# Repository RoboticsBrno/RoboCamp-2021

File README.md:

View this project on [CADLAB.io](https://cadlab.io/project/24548). 

# RoboCamp-2021

Podklady a web k Robotickému táboru 2021. 

K dispozici na [2021.robotickytabor.cz](https://2021.robotickytabor.cz/).

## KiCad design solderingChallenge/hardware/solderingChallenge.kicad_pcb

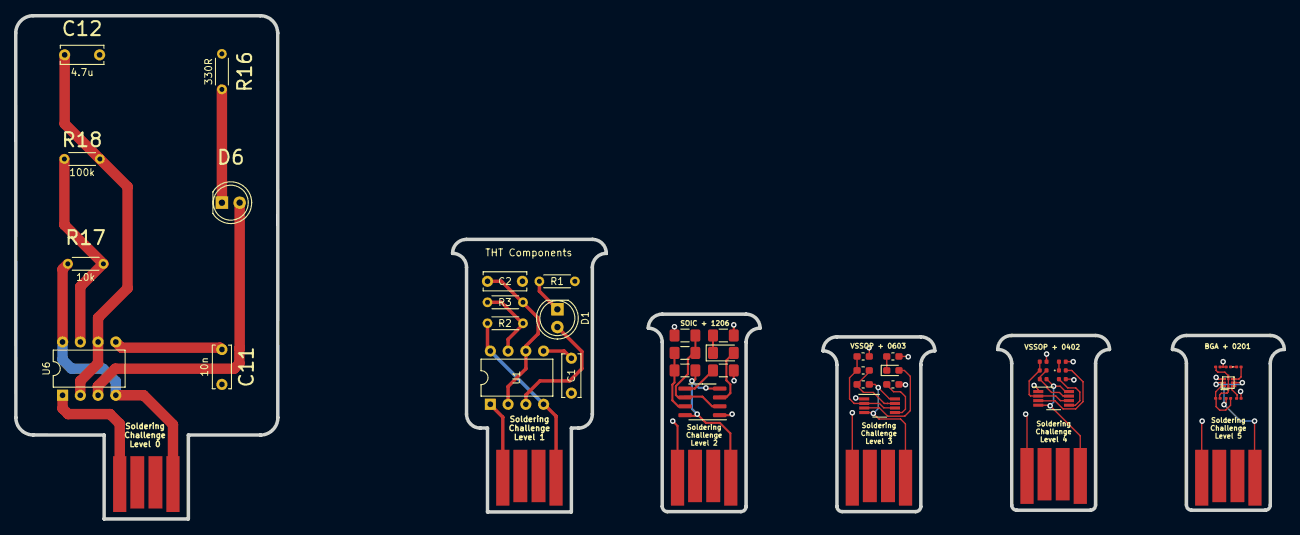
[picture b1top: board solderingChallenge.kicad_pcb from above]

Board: 2 copper layers, 181.5 x 72.0 mm, 54 parts (0 on the bottom side), 42 nets.

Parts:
B0, B1, B2, B3, B4, B5: Board
C1, C11: 10n; C_Disc_D6.0mm_W2.5mm_P5.00mm
C2, C12: 4.7u; C_Disc_D6.0mm_W2.5mm_P5.00mm
C3: 10n; C_1206_3216Metric_Pad1.42x1.75mm_HandSolder
C4: 4.7u; C_1206_3216Metric_Pad1.42x1.75mm_HandSolder
C5: 10n; C_0603_1608Metric_Pad1.05x0.95mm_HandSolder
C6: 4.7u; C_0603_1608Metric_Pad1.05x0.95mm_HandSolder
C7: 10n; C_0402_1005Metric
C8: 4.7u; C_0402_1005Metric
C9: 10n; C_0201_0603Metric
C10: 4.7u; C_0201_0603Metric
D1, D6: LED; LED_D5.0mm
D2: LED; LED_1206_3216Metric_Pad1.42x1.75mm_HandSolder
D3: LED; LED_0603_1608Metric_Pad1.05x0.95mm_HandSolder
D4: LED; LED_0402_1005Metric
D5: LED; LED_0201_0603Metric
J1, J2, J4, J6, J8, J10: USB_A; usb-PCB
R1, R16: 330R; R_Axial_DIN0204_L3.6mm_D1.6mm_P5.08mm_Horizontal
R2, R17: 10k; R_Axial_DIN0204_L3.6mm_D1.6mm_P5.08mm_Horizontal
R3, R18: 100k; R_Axial_DIN0204_L3.6mm_D1.6mm_P5.08mm_Horizontal
R4: 330R; R_1206_3216Metric_Pad1.42x1.75mm_HandSolder
R5: 10k; R_1206_3216Metric_Pad1.42x1.75mm_HandSolder
R6: 100k; R_1206_3216Metric_Pad1.42x1.75mm_HandSolder
R7: 330R; R_0603_1608Metric_Pad1.05x0.95mm_HandSolder
R8: 10k; R_0603_1608Metric_Pad1.05x0.95mm_HandSolder
R9: 100k; R_0603_1608Metric_Pad1.05x0.95mm_HandSolder
R10: 330R; R_0402_1005Metric
R11: 10k; R_0402_1005Metric
R12: 100k; R_0402_1005Metric
R13: 330R; R_0201_0603Metric
R14: 10k; R_0201_0603Metric
R15: 100k; R_0201_0603Metric
U1, U6: LM555xN; DIP-8_W7.62mm
U2: LMC555xM; SOIC-8_3.9x4.9mm_P1.27mm
U3, U4: LMC555xMM; VSSOP-8_3.0x3.0mm_P0.65mm
U5: LMC555xTP; Texas_DSBGA-8_1.43x1.41mm_Layout3x3_P0.5mm

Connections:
/Level 0 - THT/GND: C11.2, C12.2, J1.4 (GND), R16.1, U6.1 (GND)
/Level 0 - THT/VCC: J1.1 (VBUS), R17.1, U6.4 (R), U6.8 (VCC)
/Level 1 - THT/GND: C1.2, C2.2, J2.4 (GND), R1.1, U1.1 (GND)
/Level 1 - THT/VCC: J2.1 (VBUS), R2.1, U1.4 (R), U1.8 (VCC)
/Level 2 - 1206/GND: C3.2, C4.2, J4.4 (GND), R4.1, U2.1 (GND)
/Level 2 - 1206/VCC: J4.1 (VBUS), R5.1, U2.4 (R), U2.8 (VCC)
/Level 3 - 0603/GND: C5.2, C6.2, J6.4 (GND), R7.1, U3.1 (GND)
/Level 3 - 0603/VCC: J6.1 (VBUS), R8.1, U3.4 (R), U3.8 (VCC)
/Level 4 - 0402/GND: C7.2, C8.2, J8.4 (GND), R10.1, U4.1 (GND)
/Level 4 - 0402/VCC: J8.1 (VBUS), R11.1, U4.4 (R), U4.8 (VCC)
/Level 5 - 0201/GND: C9.2, C10.2, J10.4 (GND), R13.1, U5.A3 (GND)
/Level 5 - 0201/VCC: J10.1 (VBUS), R14.1, U5.A2 (VCC), U5.C2 (R)
unnamed: C1.1, U1.5 (CV)
unnamed: C2.1, R3.2, U1.2 (TR), U1.6 (THR)
unnamed: C3.1, U2.5 (CV)
unnamed: C4.1, R6.2, U2.2 (TR), U2.6 (THR)
unnamed: C5.1, U3.5 (CV)
unnamed: C6.1, R9.2, U3.2 (TR), U3.6 (THR)
unnamed: C7.1, U4.5 (CV)
unnamed: C8.1, R12.2, U4.2 (TR), U4.6 (THR)
unnamed: C9.1, U5.C1 (CV)
unnamed: C10.1, R15.2, U5.B1 (THR), U5.B3 (TR)
unnamed: C11.1, U6.5 (CV)
unnamed: C12.1, R18.2, U6.2 (TR), U6.6 (THR)
unnamed: D1.1 (K), R1.2
unnamed: D1.2 (A), U1.3 (Q)
unnamed: D2.1 (K), R4.2
unnamed: D2.2 (A), U2.3 (Q)
unnamed: D3.1 (K), R7.2
unnamed: D3.2 (A), U3.3 (Q)
unnamed: D4.1 (K), R10.2
unnamed: D4.2 (A), U4.3 (Q)
unnamed: D5.1 (K), R13.2
unnamed: D5.2 (A), U5.C3 (Q)
unnamed: D6.1 (K), R16.2
unnamed: D6.2 (A), U6.3 (Q)
unnamed: R2.2, R3.1, U1.7 (DIS)
unnamed: R5.2, R6.1, U2.7 (DIS)
unnamed: R8.2, R9.1, U3.7 (DIS)
unnamed: R11.2, R12.1, U4.7 (DIS)
unnamed: R14.2, R15.1, U5.A1 (DIS)
unnamed: R17.2, R18.1, U6.7 (DIS)

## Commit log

2020-12-13 Add template
2021-01-23 Draft first draft of smdChallenge
2021-01-24 Rename smdChallenge to solderingChallenge
2021-01-24 Finish first version of solderingChallenge
2021-02-03 Electronic Die schematic
2021-02-04 Add board
2021-02-04 Add silkscreen
2021-02-05 Add SMD power LED for testing purposes
2021-02-05 Fix +5V polygon
2021-02-05 Add mounting holes
2021-02-05 Set polygons isolation to 12 mils and width to 20 mils
2021-02-05 Add NC symbol to USB data pins
2021-02-05 Add dimensions
2021-02-05 Fix USB width
2021-02-05 Fix silkscreen layer
2021-02-05 Add JLCPCB order number location, fix SMD parts name font size
2021-02-05 Add CAM and DRU configuration
2021-02-05 Electronic Die v1.0
2021-02-11 Add v1.0 BOM (Mouser)
2021-03-22 Add RoboSvit
2021-03-22 Fix typo
2021-05-05 ElectronicDie: fix v1.0 problems - make it bigger - change resistors and diodes package size - make larger spaces between parts - minimize part types - fix PNP transistor pinout - remove SMD power LED
2021-06-03 Add target for gatema gerbers
2021-06-04 ElectronicDie v1.1 gerbers (removed JLCPCB order number label, because of fabrication in Gatema)
2021-06-08 Add USB pads
2021-06-09 Change Helceletka branding
2021-07-03 Remove extra level, add documentation
2021-07-07 Add RoboSvit Doc
2021-07-07 Remove two pictures
2021-07-07 Add CZ and EN manual link
2021-07-08 Add md doc for electron
2021-07-08 Edit schematic images
2021-07-08 Add Logic photo guide
2021-07-08 formulation
2021-07-08 Update electronicDie manual
2021-07-08 Fix electron 1. lesson - resistors
2021-07-08 Add electronicDie manual
2021-07-08 Add Logic text manual
2021-07-08 Minify images, add electronicDie manual
2021-07-08 Update schematic symbols in electron guide
2021-07-09 Add web doc
2021-07-09 Change electron schema color, resize roboSvit
2021-07-09 Add favicon, add logic fancy photos
2021-07-09 Resize electron, solderingCh images
2021-07-09 Fix typo, resize images
2021-07-09 Fix type errors and add whitespace to values
2021-07-09 Fix typos
2021-07-09 Last minute touches
2021-07-09 Empty commit
2021-07-09 Add BlackBox
2021-07-09 Fix more typos
2021-07-09 Fix typos in BlackBox
2021-07-09 Add BlackBox PDF guide
2021-07-09 add PCB of Logic
2021-07-09 Add fancy features
2021-07-09 Add note about polarity
2021-07-09 Add fancy design to index page
2021-07-09 Fix name mistake
2021-07-09 Add electron photos
2021-07-09 Add more fancy photos
2021-07-09 Add SMD fancy photo
2021-07-10 Add logo moustache
2021-07-11 Scale down ridiculously large images
2021-07-11 Move logic code example
2021-07-11 Fix resistor value
2021-07-11 fix mistake in electron guide
2021-07-11 Fix electron image
2021-07-12 Add better image to logic
2021-07-12 Add code documentation
2021-07-13 Add code examples
2021-07-13 Fix buttons Enter
2021-07-14 Add L5 for soldering challenge
2021-07-14 Add links
2021-07-15 Add projects page
2021-07-15 Add CNAME
2021-07-15 Add requirements.txt
2021-07-15 Add note about code examples
2021-07-15 Add IDE install instructions
2021-07-16 Add more projects
2021-07-21 Add links to examples
2021-07-23 Fix site name and url in `mkdocs.yml`
2021-07-23 README: add basic info and link to web
2021-07-23 Backlink to CADLAB.io has been added.
2022-02-01 ElectronicDie v1.2: more resistant to assembly errors - resistors with same value grouped together - diodes grouped together - larger spaces between parts - 2k2 resistor replaced with 2 × 1k (so only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
2022-03-07 Add L0 to soldering challenge
2022-03-17 ElectronicDie v1.2: Add logos, freeze version and add gerbers
2022-07-07 Fix USB size on L0
2022-07-14 Update to newer version, add link to doc, fix 404
2022-07-18 Rotate capacitor on L0
2023-06-30 Add new packages, team
2024-03-01 Deployed 5e6599f with MkDocs version: 1.4.3
2025-02-23 Enhance README with modal for version update and improve content layout
2025-02-23 Update README to include link for new version and adjust modal buttons
2025-03-01 Deployed 798b591 with MkDocs version: 1.4.3
